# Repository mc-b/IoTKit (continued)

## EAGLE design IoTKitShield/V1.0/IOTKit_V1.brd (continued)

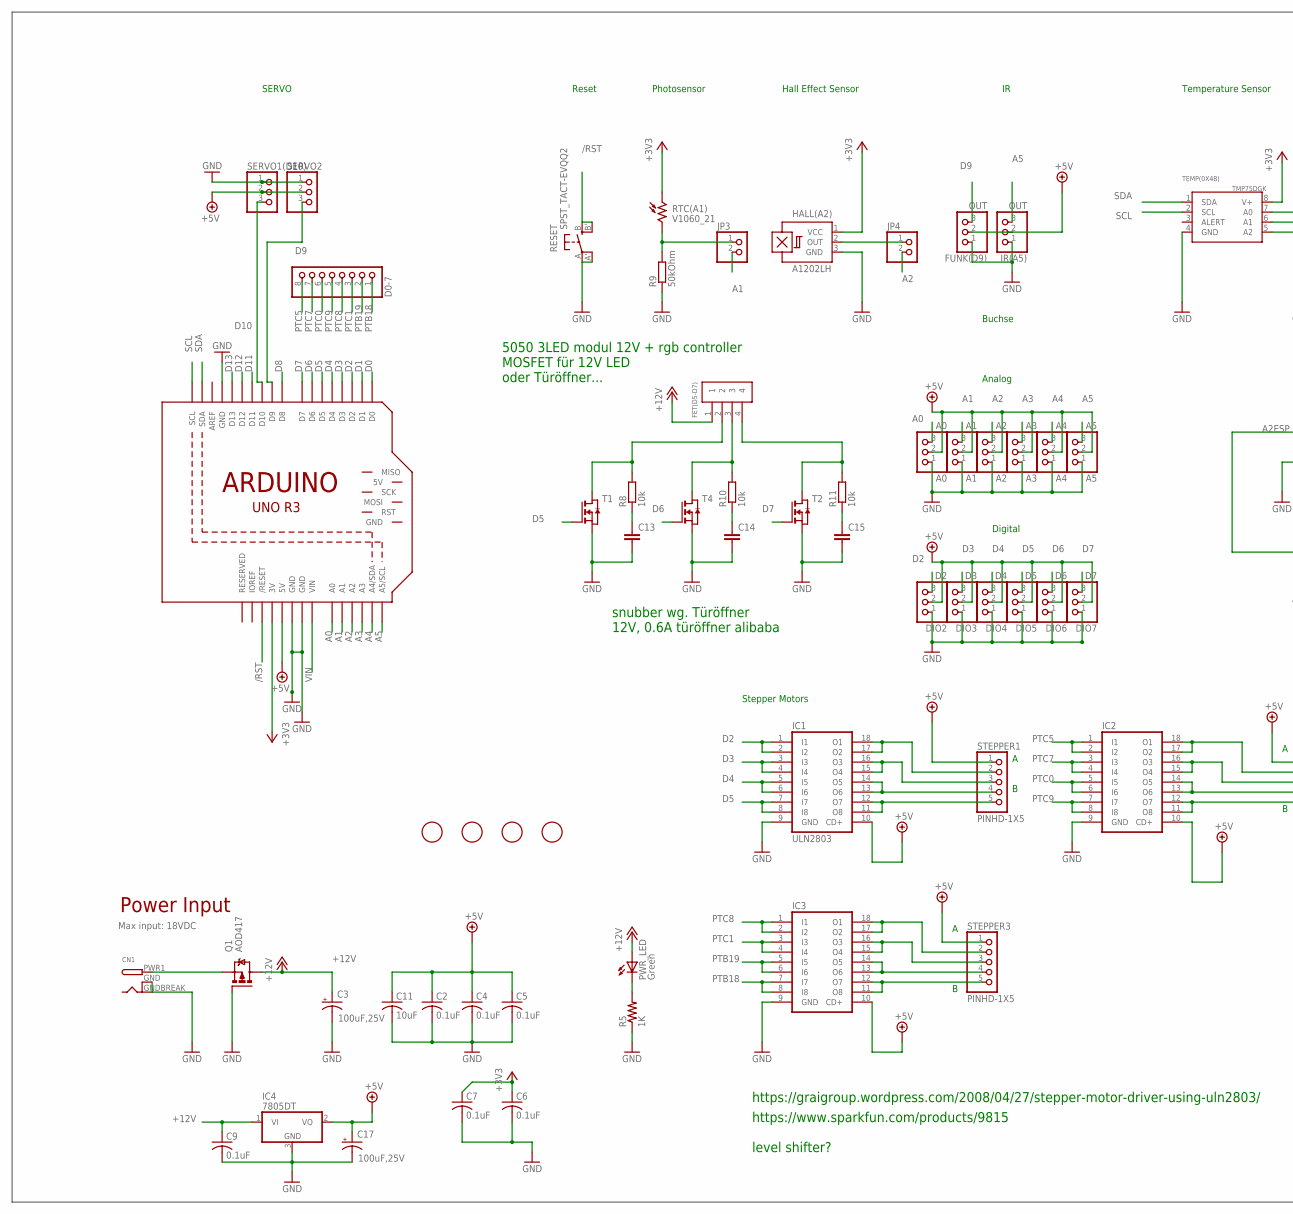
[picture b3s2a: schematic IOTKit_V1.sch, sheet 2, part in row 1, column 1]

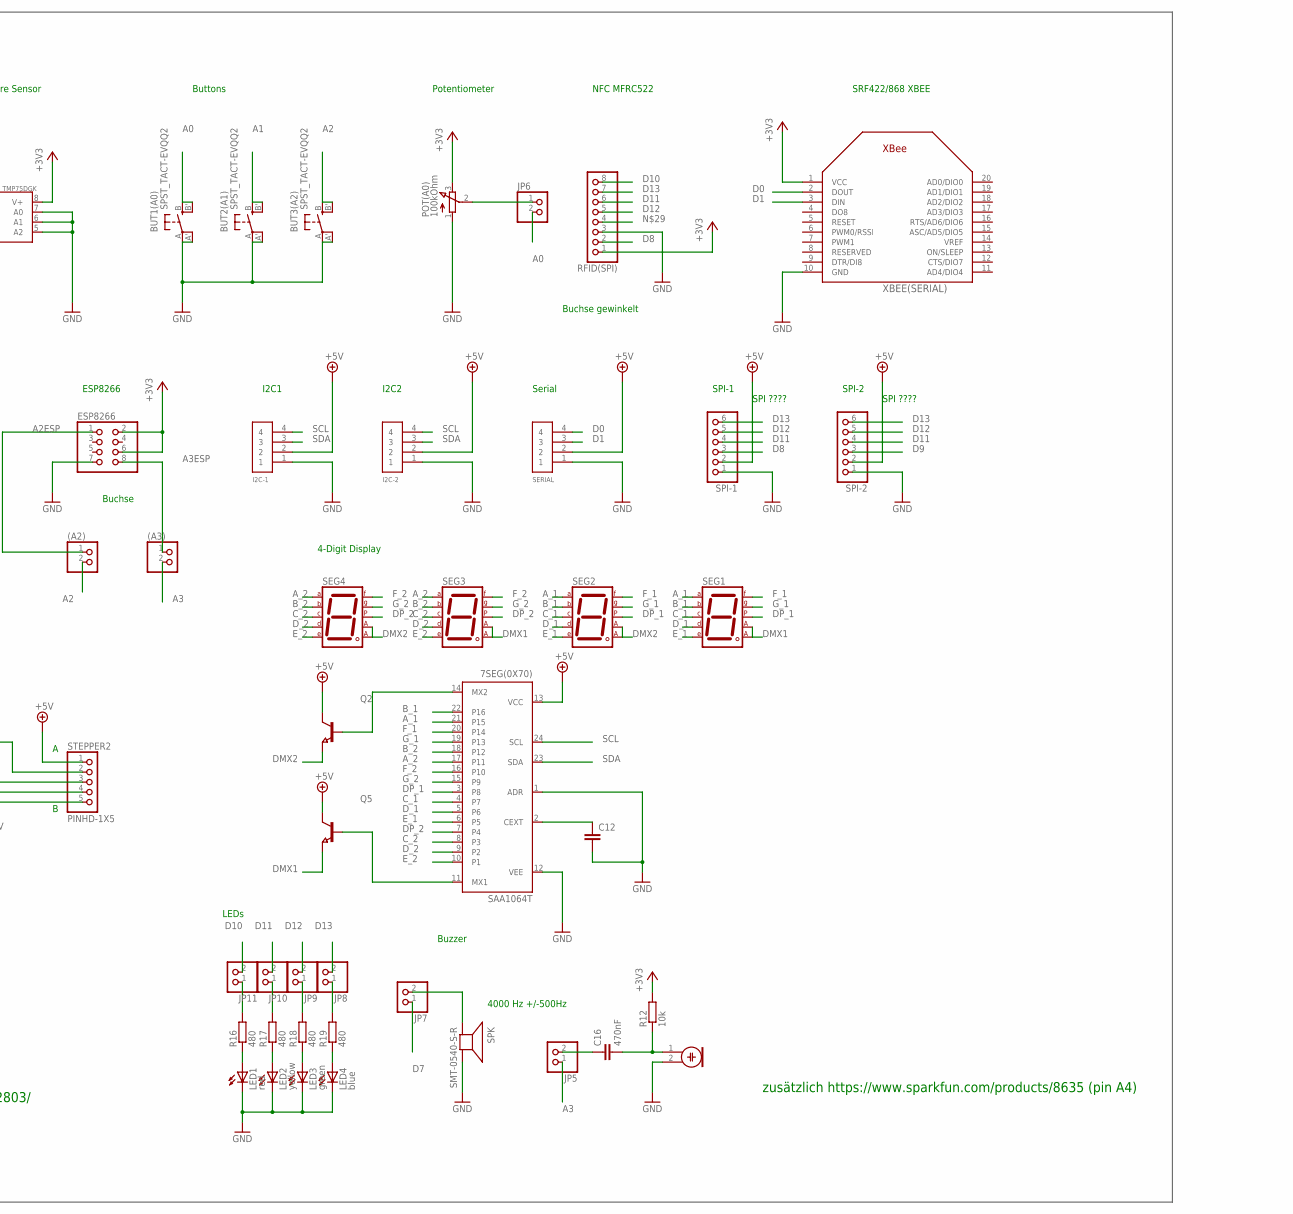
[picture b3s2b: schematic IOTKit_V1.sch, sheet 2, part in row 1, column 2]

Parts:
7SEG(0X70): SAA1064T; SO24
(A2), (A3): PINHD-1X2; 1X02_LINE
A0: A0; 1X03_LINE
A1: A1; 1X03_LINE
A2: A2; 1X03_LINE
A3: A3; 1X03_LINE
A4: A4; 1X03_LINE
A5: A5; 1X03_LINE
BUT1(A0), BUT2(A1), BUT3(A2): SPST_TACT-EVQQ2; EVQ-Q2
C2, C4, C5, C6, C7: 0.1uF; C0603K
C3, C17: 100uF,25V; NIPPON_F80
C9: 0.1uF; C0805K
C11: 10uF; C0805K
C12, C13, C14, C15: C-EUC0603; C0603
C16: 470nF; C0603
CN1: DCBARRELSMT; DCJACK_2MM_SMT
D0-7: PINHD-1X8CLEANBIG; 1X08-CLEANBIG
DIO2: D2; 1X03_LINE
DIO3: D3; 1X03_LINE
DIO4: D4; 1X03_LINE
DIO5: D5; 1X03_LINE
DIO6: D6; 1X03_LINE
DIO7: D7; 1X03_LINE
ESP8266: PINHD-2X4; 2X04
FET(D5-D7): 1X4; 1X04_LINE
FUNK(D9): OUT; 1X03_LINE
HALL(A2): A1202LH; SOT23-W
I2C-1, I2C-2: 1X4; 1X04_LINE
IC1: ULN2803; SO18W
IC2, IC3: ULN2803ASO18W; SO18W
IC4: 7805DT; TO252
IR(A5): OUT; 1X03_LINE
JP3, JP4, JP5, JP6, JP7, JP8, JP9, JP10, JP11: PINHD-1X2; 1X02_LINE
LED1: red; CHIP-LED0603
LED2: yellow; CHIP-LED0603
LED3: green; CHIP-LED0603
LED4: blue; CHIP-LED0603
MIC(A3): ELECTRET_MICROPHON-WM-62PC/62PK; WM-62PC/62PK
POT(A0): 100kOhm; EVUF
PWR_LED: Green; CHIP-LED0805
Q1: AOD417; D-PAK_TO252AA
Q2, Q5: NPN-TRANSISTOR_SOT23; SOT23
R5: 1K; R0805
R8, R10, R11: 10k; R0805
R9: 50kOhm; R0603
R12: 10k; R0603
R16, R17, R18, R19: 480; R0603
RESET: SPST_TACT-EVQQ2; EVQ-Q2
RFID(SPI): PINHD-1X8BIG; 1X08-BIG
RTC(A1): V1060_21; TO-5_V10
SEG1, SEG2, SEG3, SEG4: 7SEG-MCK; 7SEG-7
SERIAL: 1X4; 1X04_LINE
SERVO1(D10), SERVO2: PINHD-1X3; 1X03
SPI-1, SPI-2: PINHD-1X6B; 1X06-BIG
SPK: SMT-0540-S-R
STEPPER1, STEPPER2, STEPPER3: PINHD-1X5; 1X05
T1, T2, T4: NMOSSOT223; SOT223
TEMP(0X48): TMP75DGK; MSOP8
U$1, U$2, U$3, U$6: FIDUCIAL; FIDUCIAL_1MM
U$5: ARDUINO_R3_ICSP_NODIM; ARDUINOR3_ICSP_NODIM
XBEE(SERIAL): XBEE

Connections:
+3V3: C6.1, C7.1, ESP8266.2, ESP8266.6, HALL(A2).1 (VCC), POT(A0).3 (E), R12.2, RFID(SPI).1, RTC(A1).1, TEMP(0X48).8 (V+), U$5.3V, XBEE(SERIAL).1 (VCC)
+5V: 7SEG(0X70).13 (VCC), A0.2, A1.2, A2.2, A3.2, A4.2, A5.2, C2.1, C4.1, C5.1, C11.1, C17.+, DIO2.2, DIO3.2, DIO4.2, DIO5.2, DIO6.2, DIO7.2, FUNK(D9).2, I2C-1.2, I2C-2.2, IC1.10 (CD+), IC2.10 (CD+), IC3.10 (CD+), IC4.2 (VO), IR(A5).2, Q2.3 (C), Q5.3 (C), SERIAL.2, SERVO1(D10).2, SERVO2.2, SPI-1.2, SPI-2.2, STEPPER1.1, STEPPER2.1, STEPPER3.1, U$5.5V; also elsewhere on the board
+12V: C3.+, C9.1, FET(D5-D7).1, IC4.1 (VI), PWR_LED.A, Q1.4 (D); also elsewhere on the board
/RST: RESET.B (S), RESET.B' (S1), U$5.RESET (/RESET)
A0: A0.3, BUT1(A0).B (S), BUT1(A0).B' (S1), JP6.2, U$5.A0
A1: A1.3, BUT2(A1).B (S), BUT2(A1).B' (S1), JP3.2, U$5.A1
A2: (A2).2, A2.3, BUT3(A2).B (S), BUT3(A2).B' (S1), JP4.2, U$5.A2
A2ESP: (A2).1, ESP8266.1
A3: (A3).2, A3.3, JP5.1, U$5.A3
A3ESP: (A3).1, ESP8266.8
A4: A4.3, U$5.A4 (A4/SDA)
A5: A5.3, IR(A5).3, U$5.A5 (A5/SCL)
A_1: 7SEG(0X70).21 (P15), SEG1.7 (A), SEG2.7 (A)
A_2: 7SEG(0X70).17 (P11), SEG3.7 (A), SEG4.7 (A)
B_1: 7SEG(0X70).22 (P16), SEG1.6 (B), SEG2.6 (B)
B_2: 7SEG(0X70).18 (P12), SEG3.6 (B), SEG4.6 (B)
C_1: 7SEG(0X70).4 (P7), SEG1.4 (C), SEG2.4 (C)
C_2: 7SEG(0X70).8 (P3), SEG3.4 (C), SEG4.4 (C)
D0: SERIAL.4, U$5.D0, XBEE(SERIAL).2 (DOUT)
D1: SERIAL.3, U$5.D1, XBEE(SERIAL).3 (DIN)
D2: DIO2.3, IC1.1 (I1), IC1.2 (I2), U$5.D2; also elsewhere on the board
D3: DIO3.3, IC1.3 (I3), IC1.4 (I4), U$5.D3; also elsewhere on the board
D4: DIO4.3, IC1.5 (I5), IC1.6 (I6), U$5.D4; also elsewhere on the board
D5: DIO5.3, IC1.7 (I7), IC1.8 (I8), T1.1 (G), U$5.D5; also elsewhere on the board
D6: DIO6.3, T4.1 (G), U$5.D6; also elsewhere on the board
D7: DIO7.3, JP7.1, T2.1 (G), U$5.D7; also elsewhere on the board
D8: RFID(SPI).2, SPI-1.3, U$5.D8
D9: FUNK(D9).3, SERVO2.3, SPI-2.3, U$5.D9
D10: JP11.2, RFID(SPI).8, SERVO1(D10).3, U$5.D10
D11: JP10.2, RFID(SPI).6, SPI-1.4, SPI-2.4, U$5.D11
D12: JP9.2, RFID(SPI).5, SPI-1.5, SPI-2.5, U$5.D12
D13: JP8.2, RFID(SPI).7, SPI-1.6, SPI-2.6, U$5.D13
DMX1: Q5.2 (E), SEG1.3 (CA1), SEG1.8 (CA2), SEG3.3 (CA1), SEG3.8 (CA2)
DMX2: Q2.2 (E), SEG2.3 (CA1), SEG2.8 (CA2), SEG4.3 (CA1), SEG4.8 (CA2)
DP_1: 7SEG(0X70).3 (P8), SEG1.5 (DP), SEG2.5 (DP)
DP_2: 7SEG(0X70).7 (P4), SEG3.5 (DP), SEG4.5 (DP)
D_1: 7SEG(0X70).5 (P6), SEG1.2 (D), SEG2.2 (D)
D_2: 7SEG(0X70).9 (P2), SEG3.2 (D), SEG4.2 (D)
E_1: 7SEG(0X70).6 (P5), SEG1.1 (E), SEG2.1 (E)
E_2: 7SEG(0X70).10 (P1), SEG3.1 (E), SEG4.1 (E)
F_1: 7SEG(0X70).20 (P14), SEG1.9 (F), SEG2.9 (F)
F_2: 7SEG(0X70).16 (P10), SEG3.9 (F), SEG4.9 (F)
GND: 7SEG(0X70).1 (ADR), 7SEG(0X70).12 (VEE), A0.1, A1.1, A2.1, A3.1, A4.1, A5.1, BUT1(A0).A, BUT1(A0).A' (P1), BUT2(A1).A, BUT2(A1).A' (P1), BUT3(A2).A, BUT3(A2).A' (P1), C2.2, C3.-, C4.2, C5.2, C6.2, C7.2, C9.2, C11.2, C12.2, C13.2, C14.2, C15.2, C17.-, CN1.GND (GNDBREAK), CN1.GNDBREAK (GND), DIO2.1, DIO3.1, DIO4.1, DIO5.1, DIO6.1, DIO7.1, ESP8266.7, FUNK(D9).1, HALL(A2).3 (GND), I2C-1.1, I2C-2.1, IC1.9 (GND), IC2.9 (GND), IC3.9 (GND), IC4.3 (GND), IR(A5).1, LED1.C, LED2.C, LED3.C, LED4.C, MIC(A3).2, POT(A0).1 (A), Q1.1 (G), R5.1, R9.1, RESET.A, RESET.A' (P1), RFID(SPI).3, SERIAL.1, SERVO1(D10).1, SERVO2.1, SPI-1.1, SPI-2.1, SPK.+ (-), T1.3 (S), T2.3 (S), T4.3 (S), TEMP(0X48).4 (GND), TEMP(0X48).5 (A2), TEMP(0X48).6 (A1), TEMP(0X48).7 (A0), U$5.GND, U$5.GND@1 (GND), U$5.GND@3 (GND), XBEE(SERIAL).10 (GND); also elsewhere on the board
G_1: 7SEG(0X70).19 (P13), SEG1.10 (G), SEG2.10 (G)
G_2: 7SEG(0X70).15 (P9), SEG3.10 (G), SEG4.10 (G)
unnamed: CN1.PWR1 (PWR), Q1.3 (S)
unnamed: JP3.1, R9.2, RTC(A1).2
unnamed: HALL(A2).2 (OUT), JP4.1
unnamed: C16.1, JP5.2
unnamed: JP6.1, POT(A0).2 (S)
unnamed: JP7.2, SPK.- (+)
unnamed: JP11.1, R16.2
unnamed: JP10.1, R17.2
unnamed: JP9.1, R18.2
unnamed: JP8.1, R19.2
unnamed: LED1.A, R16.1
unnamed: LED2.A, R17.1
unnamed: LED3.A, R18.1
unnamed: LED4.A, R19.1
unnamed: IC2.11 (O8), IC2.12 (O7), STEPPER2.5
unnamed: IC2.13 (O6), IC2.14 (O5), STEPPER2.4
unnamed: IC2.15 (O4), IC2.16 (O3), STEPPER2.3
unnamed: IC2.17 (O2), IC2.18 (O1), STEPPER2.2
unnamed: 7SEG(0X70).14 (MX2), Q2.1 (B)
unnamed: 7SEG(0X70).11 (MX1), Q5.1 (B)
unnamed: 7SEG(0X70).2 (CEXT), C12.1
unnamed: C13.1, R8.1
unnamed: FET(D5-D7).2, R8.2, T1.2 (D), T1.4 (D)
unnamed: C14.1, R10.1
unnamed: FET(D5-D7).3, R10.2, T4.2 (D), T4.4 (D)
unnamed: C15.1, R11.1
unnamed: FET(D5-D7).4, R11.2, T2.2 (D), T2.4 (D)
unnamed: C16.2, MIC(A3).1, R12.1
unnamed: IC1.11 (O8), IC1.12 (O7), STEPPER1.5
unnamed: IC1.13 (O6), IC1.14 (O5), STEPPER1.4
unnamed: IC1.15 (O4), IC1.16 (O3), STEPPER1.3
unnamed: IC1.17 (O2), IC1.18 (O1), STEPPER1.2
unnamed: IC3.11 (O8), IC3.12 (O7), STEPPER3.5
unnamed: IC3.13 (O6), IC3.14 (O5), STEPPER3.4
unnamed: IC3.15 (O4), IC3.16 (O3), STEPPER3.3
unnamed: IC3.17 (O2), IC3.18 (O1), STEPPER3.2
PTB18: D0-7.1, IC3.7 (I7), IC3.8 (I8)
PTB19: D0-7.2, IC3.5 (I5), IC3.6 (I6)
PTC0: D0-7.6, IC2.5 (I5), IC2.6 (I6)
PTC1: D0-7.3, IC3.3 (I3), IC3.4 (I4)
PTC5: D0-7.8, IC2.1 (I1), IC2.2 (I2)
PTC7: D0-7.7, IC2.3 (I3), IC2.4 (I4)
PTC8: D0-7.4, IC3.1 (I1), IC3.2 (I2)
PTC9: D0-7.5, IC2.7 (I7), IC2.8 (I8)
PWR_LED: PWR_LED.C, R5.2
SCL: 7SEG(0X70).24 (SCL), I2C-1.4, I2C-2.4, TEMP(0X48).2 (SCL), U$5.SCL
SDA: 7SEG(0X70).23 (SDA), I2C-1.3, I2C-2.3, TEMP(0X48).1 (SDA), U$5.SDA
VIN: U$5.VIN

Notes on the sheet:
ESP8266
Analog
Temperature Sensor
Buttons
Hall Effect Sensor
Reset
Photosensor
Potentiometer
I2C1
I2C2
Serial
SPI-1
SPI-2
SPI ????
Digital
4-Digit Display
Buzzer
4000 Hz +/-500Hz
LEDs
NFC MFRC522
SRF422/868 XBEE
https://www.sparkfun.com/products/9815
level shifter?
https://graigroup.wordpress.com/2008/04/27/stepper-motor-driver-using-uln2803/
MOSFET für 12V LED oder Türöffner...
5050 3LED modul 12V + rgb controller
snubber wg. Türöffner 12V, 0.6A türöffner alibaba
zusätzlich https://www.sparkfun.com/products/8635 (pin A4)
Stepper Motors
Power Input
Max input: 18VDC
Buchse
Buchse gewinkelt
SERVO

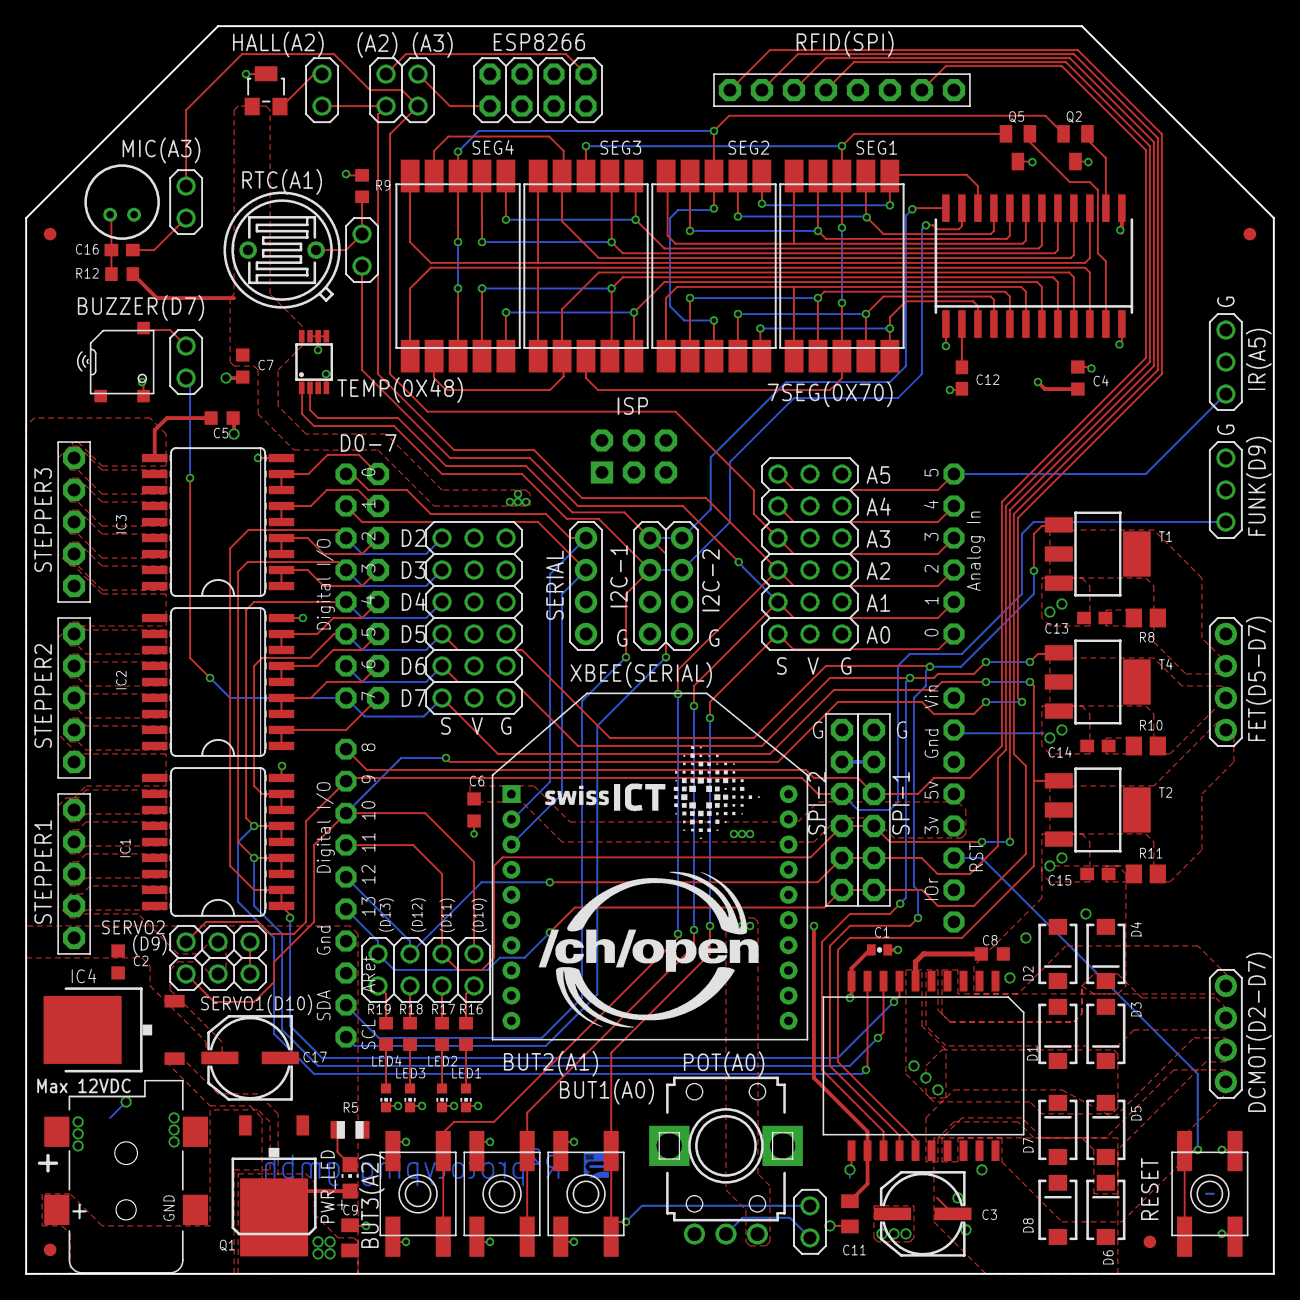
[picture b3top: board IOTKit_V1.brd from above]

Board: 2 copper layers, 99.1 x 99.1 mm, 113 parts (1 on the bottom side), 96 nets.

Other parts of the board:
U$4: R2_2MM

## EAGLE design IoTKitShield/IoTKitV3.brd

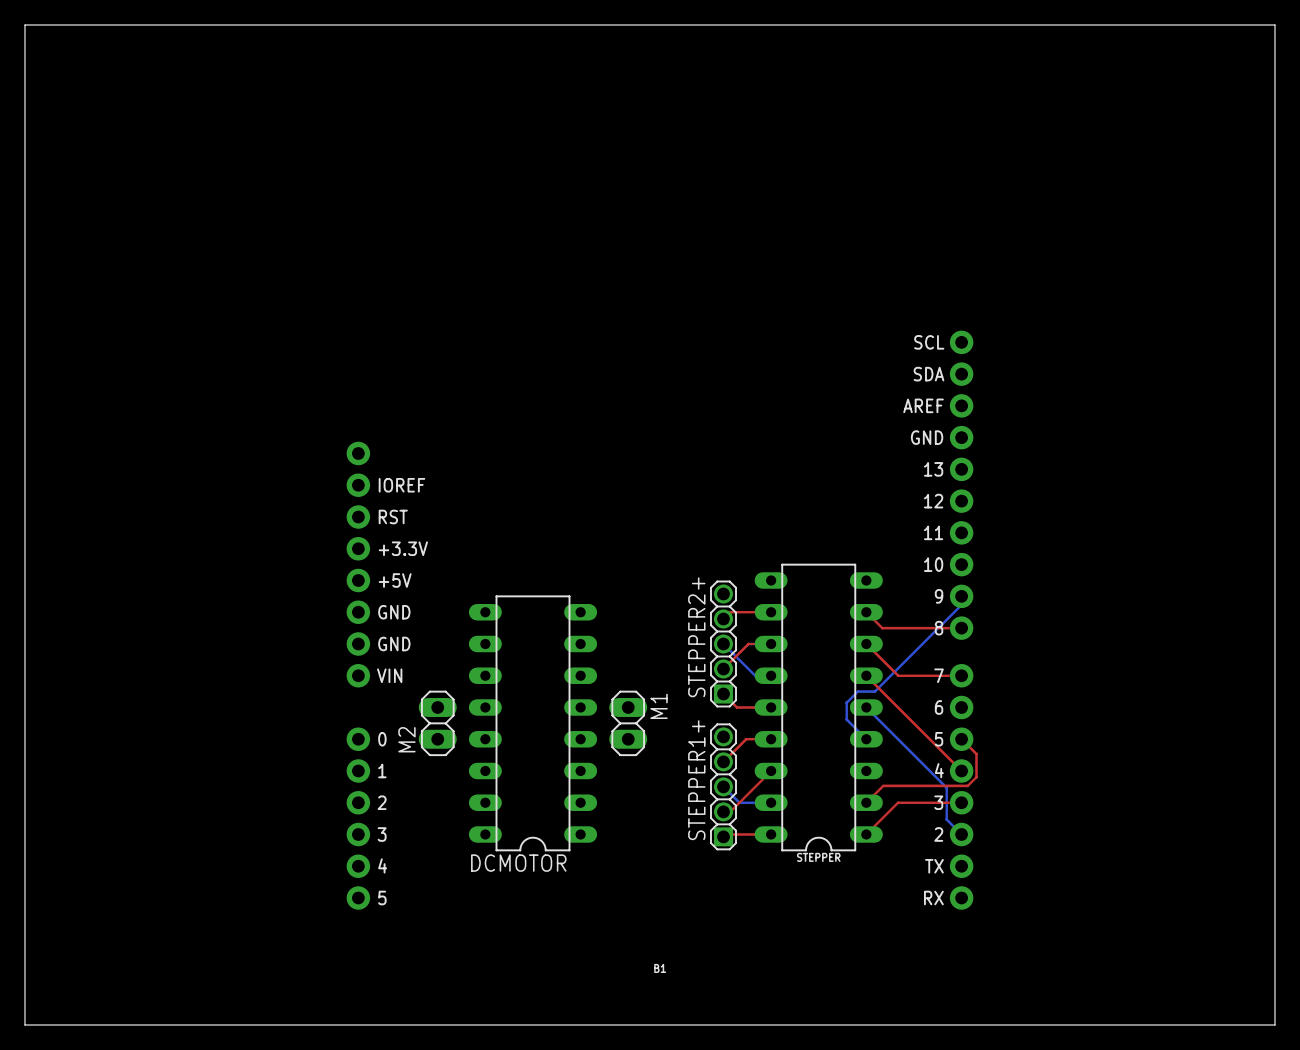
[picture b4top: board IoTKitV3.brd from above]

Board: 2 copper layers, 100.0 x 80.0 mm, 7 parts (0 on the bottom side), 22 nets.

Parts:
B1: ARDUINO_UNO_R3_SHIELDBASIC; UNO_R3_SHIELD
DCMOTOR: L293D; DIL16
M1, M2: 1X02
STEPPER: DIL18
STEPPER1+, STEPPER2+: 1_05X2MM

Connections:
+5V: B1.5V, DCMOTOR.8, DCMOTOR.16, STEPPER.10, STEPPER1+.5, STEPPER2+.5
D2: B1.D2, DCMOTOR.2, STEPPER.5
D3: B1.D3, DCMOTOR.1, STEPPER.1
D4: B1.D4, DCMOTOR.7, STEPPER.6
D5: B1.D5, DCMOTOR.9, STEPPER.2
D6: B1.D6, DCMOTOR.10, STEPPER.3
D7: B1.D7, DCMOTOR.15, STEPPER.7
D8: B1.D8, STEPPER.8
D9: B1.D9, STEPPER.4
GND: B1.GND@0, B1.GND@1, B1.GND@2, DCMOTOR.4, DCMOTOR.5, DCMOTOR.12, DCMOTOR.13, STEPPER.9
unnamed: STEPPER.18, STEPPER1+.1
unnamed: STEPPER.17, STEPPER1+.2
unnamed: STEPPER.16, STEPPER1+.3
unnamed: STEPPER.15, STEPPER1+.4
unnamed: STEPPER.14, STEPPER2+.1
unnamed: STEPPER.13, STEPPER2+.2
unnamed: STEPPER.12, STEPPER2+.3
unnamed: STEPPER.11, STEPPER2+.4
unnamed: DCMOTOR.3, M1.2
unnamed: DCMOTOR.6, M1.1
unnamed: DCMOTOR.14, M2.1
unnamed: DCMOTOR.11, M2.2

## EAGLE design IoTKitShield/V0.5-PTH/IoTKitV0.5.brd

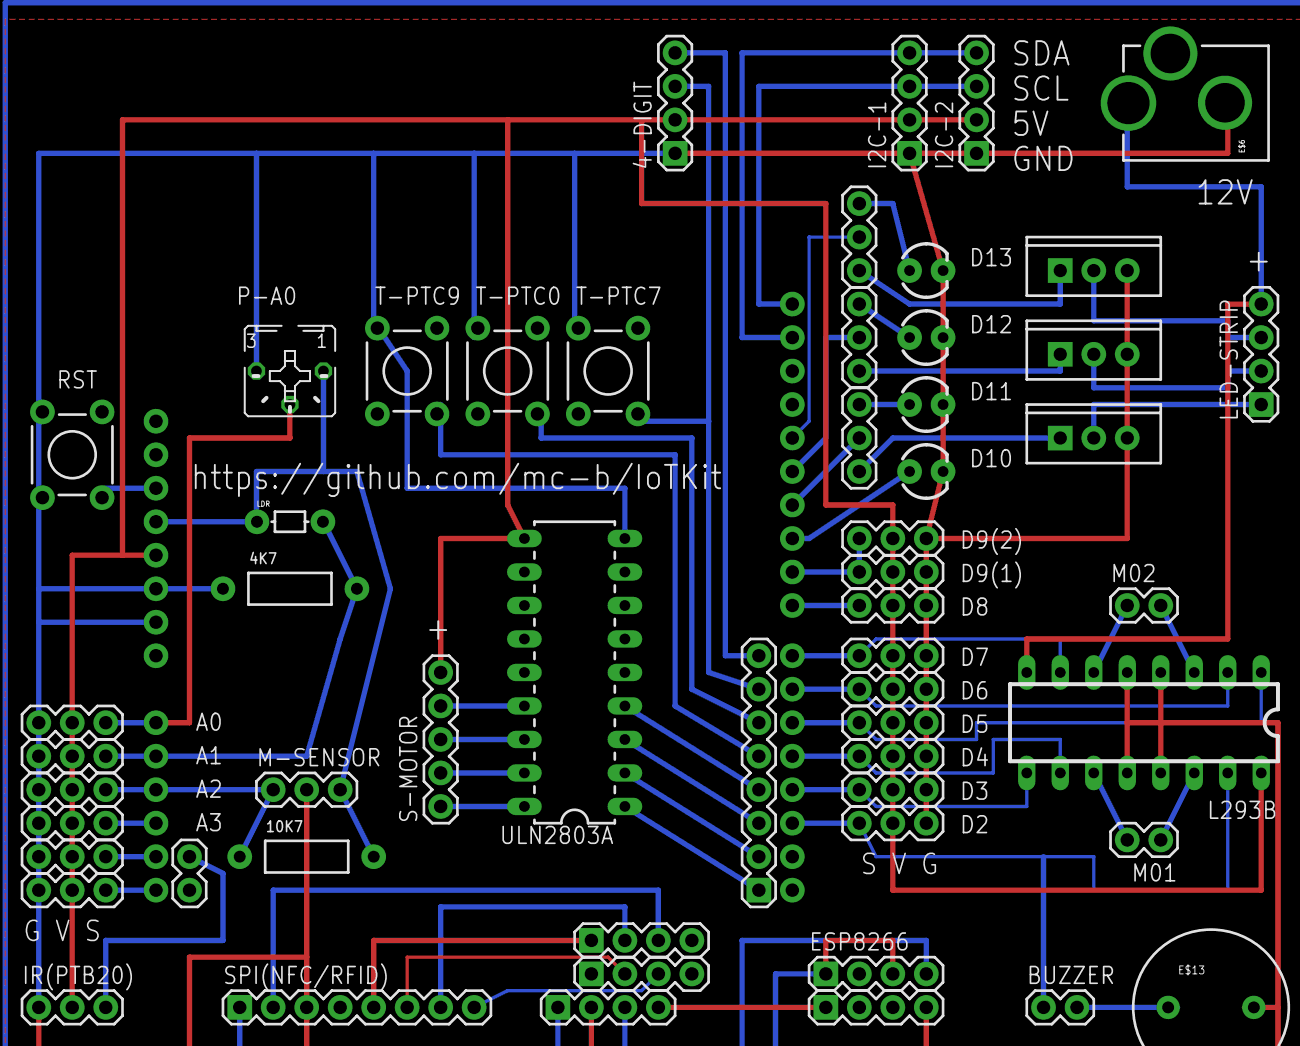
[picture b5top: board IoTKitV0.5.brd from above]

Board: 2 copper layers, 56 parts (0 on the bottom side), 56 nets.

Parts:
4-DIGIT: 1X04
4K7, 10K7: AXIAL-0.4
A0, A1, A2, A3, A4, A5: 1X03
BUZZER: 1X02
D2, D3, D4, D5, D6, D7, D8, D9(1), D9(2): 1X03
D10, D11, D12, D13: LED3MM
E$1: UNO_R3_SHIELD_NOLABELS
E$2, E$3, E$4: TO220-IGO
E$5: 1X08
E$6: POWER_JACK_PTH_LOCK
E$7, E$9, E$15: 1X03
E$8: 1X02
E$10, E$11, E$12, E$14: 1X04
E$13: BUZZER-12MM
ESP8266: 1X04
I2C-1, I2C-2: 1X04
IR(PTB20): 1X03
L293B: DIL16
LDR: AXIAL-5MM
LED-STRIP: 1X04
M01, M02: 1X02
M-SENSOR: 1X03
P-A0: B25P
RST: TACTILE-PTH
S-MOTOR: 1X05
SPI(NFC/RFID): 1X08
T-PTC0, T-PTC7, T-PTC9: TACTILE-PTH
ULN2803A: DIL18

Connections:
3V3: 10K7.P$2, E$1.3.3V, M-SENSOR.3, P-A0.A
5V: 4-DIGIT.2, A0.2, A1.2, A2.2, A3.2, A4.2, A5.2, D2.2, D3.2, D4.2, D5.2, D6.2, D7.2, D8.2, D9(1).2, D9(2).2, E$1.5V, I2C-1.2, I2C-2.2, IR(PTB20).2, L293B.16, S-MOTOR.5, ULN2803A.10
GND: 4-DIGIT.1, 4K7.P$1, A0.3, A1.3, A2.3, A3.3, A4.3, A5.3, D2.3, D3.3, D4.3, D5.3, D6.3, D7.3, D8.3, D9(1).3, D9(2).3, D10.K, D11.K, D12.K, D13.K, E$1.GND@0, E$1.GND@1, E$2.OUT, E$3.OUT, E$4.OUT, E$12.2, E$14.4, I2C-1.1, I2C-2.1, IR(PTB20).1, L293B.4, L293B.5, L293B.12, L293B.13, M-SENSOR.2, P-A0.E, SPI(NFC/RFID).3, ULN2803A.9
S$1: E$12.1, ESP8266.1, ESP8266.3, SPI(NFC/RFID).1
S$2: E$4.GND, LED-STRIP.1
S$3: E$2.GND, LED-STRIP.2
S$4: E$3.GND, LED-STRIP.3
S$5: E$12.3, ESP8266.4
S$6: E$12.4, E$14.1
S$7: D9(1).1, D9(2).1, E$1.D9
S$8: 4-DIGIT.4, E$5.8
S$9: E$1.D11, E$15.2
S$10: E$1.D12, E$9.2
S$11: D8.1, E$1.D8
S$12: E$1.D13, E$7.2
S$14: D11.A, E$15.3
S$15: D12.A, E$9.3
S$16: D13.A, E$7.3
S$17: E$3.IN, E$7.1
S$19: E$5.1, ULN2803A.1
S$20: E$5.2, ULN2803A.2
S$21: E$5.3, ULN2803A.3
S$22: E$5.4, ULN2803A.4
S$23: S-MOTOR.1, ULN2803A.18
S$24: S-MOTOR.2, ULN2803A.17
S$25: S-MOTOR.3, ULN2803A.16
S$26: S-MOTOR.4, ULN2803A.15
S$27: L293B.6, M02.1
S$28: L293B.3, M02.2
S$29: L293B.14, M01.1
S$30: L293B.11, M01.2
S$31: E$2.IN, E$9.1
S$32: A3.1, E$1.A3
S$33: A4.1, E$1.A4
S$34: E$4.IN, E$15.1
S$35: A5.1, E$1.A5
S$36: 10K7.P$1, A2.1, E$1.A2, M-SENSOR.1
S$37: A0.1, E$1.A0, P-A0.S
S$38: E$10.3, SPI(NFC/RFID).2
S$39: E$11.3, SPI(NFC/RFID).8
S$40: E$10.2, SPI(NFC/RFID).7
S$41: E$10.1, SPI(NFC/RFID).5
S$42: E$11.2, SPI(NFC/RFID).6
S$50: 4K7.P$2, A1.1, E$1.A1
V12: L293B.8, LED-STRIP.4
W2: BUZZER.1, D2.1, E$1.D2, L293B.15
W3: D3.1, E$1.D3, L293B.9
W4: D4.1, E$1.D4, L293B.10
W5: D5.1, E$1.D5, L293B.1
W6: D6.1, E$1.D6, L293B.2
W7: D7.1, E$1.D7, L293B.7
W10: D10.A, E$1.D10
WB20: E$8.2, IR(PTB20).3
WC9: 4-DIGIT.3, E$5.7
WSCL: E$1.SDA, I2C-1.4, I2C-2.4
WSDA: E$1.SCL, I2C-1.3, I2C-2.3

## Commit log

2015-03-13 Einfache Web-App
2015-03-13 Falscher Dateiname
2015-08-05 Beispiele fuer lokale Compilation
2015-08-05 Beispiel fuer lokale Compilation (nur Beispiel Makefile)
2015-08-15 Ausgesuchte Testprogramme adaptiert auf Eclipse und gcc4mbed
2015-08-28 Eclipse SmartHome Binding fuer IoTKit SMD Shield
2015-08-28 Temp (I2C) und RGB LED Strip impl.
2015-09-07 Copyright bereinigt
2015-09-14 Im Original auf mbed.org geaendert
2015-09-14 Steuert jetzt auf cygwin zu
2015-11-05 Dockerfile fuer leshan
2015-11-05 Beschreibung
2015-11-05 Test und Infrastruktur ergaenzt
2015-11-05 Apache REST Docker Image
2015-11-05 Integration MySQL
2015-11-05 Formatierung
2015-11-05 Format
2015-11-13 Feintuning
2015-11-13 IoTKit Shield Version 0.5 und V1.0
2015-11-13 IoTKit Version V2.0
2015-11-13 Modem Korrekturen
2015-11-13 Detailkorrekturen
2015-11-13 Beschreibungen
2015-11-13 CAD Teile zum IoTKit
2015-11-13 CAD Teile
2015-11-13 Makefile um Docker zu vereinfachen
2015-11-13 Makefile
2015-11-13 mosquitto Docker image fuer IoTKit
2015-11-13 openhab2 Docker
2015-11-13 Jenkins Docker Image
2015-11-13 Platzhalter weitere Images
2015-11-13 FROM Versionen abgestimmt
2015-11-14 Wetty (Web + tty) Image
2015-11-14 Ergaenzt
2015-11-14 Globaler Makefile
2015-11-14 clean
2015-11-14 Hostname setzen
2015-11-14 Apache Reverse Proxy und Ports abgestimmt
2015-11-14 Grundkonfiguration
2015-11-14 Bereinigt
2015-11-14 Feintuning - Zugriff auf MySQL Server
2015-11-14 FHEM Image
2015-11-15 Test Proxy Einstellungen
2015-11-15 Relative statt fixe URL's
2015-11-15 Kura Grundimage
2015-11-15 Fehler apt-get update erledigt
2015-11-16 Repository wetty autom. holen beim builden
2015-11-16 init.d Initscript um alle Docker Container zu starten
2015-11-16 stop verschnellert
2015-11-16 Explizites Stoppen bei make run
2015-11-16 alten Container bei run verwerfen
2015-11-16 Startup fuer Docker Images
2015-11-17 Zip HACK eleminiert
2015-11-17 Mosquitto Server
2015-11-17 Ergaenzt um CoAP
2015-11-17 Optimiert
2015-11-17 Logs eingefuegt
2015-11-17 Usage eingefuert
2015-11-17 Kommentar verbessert
2015-11-17 Ergaenzt um LWM2M Client
2015-11-18 Ausgabe Pub Message auf stdout
2015-11-18 cgi-bin Script um Docker Logs im Browser auszugeben
2015-11-19 IotKit Beispiele ergaenzt
2015-11-22 ThingSpeak Image
2015-11-22 thingSpeak nachgetragen
2015-11-22 Netzwerk uebersicht
2015-11-23 Zusteuerung neuste Doker Version
2015-11-23 Cordova Grundgeruest
2015-11-23 Abgestimmt mit Android SDK Version
2015-11-23 simpleAPP abgestimmt auf Apache Cordova
2015-11-23 Optimiert, Jenkins Jobs
2015-11-23 Umfangreicheres Beispiel
2015-11-23 IoTKit App Sample
2015-11-23 cd korrigiert
2015-11-23 Release entfernt gibt Probleme beim Installieren
2015-11-24 GCC4mbed und mbed V2 Job eingefuegt
2015-11-24 Volume um Container als Build Umgebung zu verwenden
2015-11-26 web-terminal als Alternative zu wetty
2015-11-26 Jenkins Jobs
2015-11-26 Script fuer Netzwerkuebersicht
2015-11-27 Eigene Jenkins Umgebung fuer Java Jobs erstellt.
2015-11-27 Anpassungen Raspberry Pi
2015-11-28 Proxy Material
2015-11-28 iot-stick Umgebung
2015-11-28 Installation Docker und Standard Umgebung - nicht getestet
2015-11-28 : fehlte
2015-11-28 Falsches Verzeichnis
2015-11-28 Start Docker bei Systemstart
2015-11-28 Push und Pull
2015-11-28 Fehlerkorrektur, Erweiterung pull Rasppberry Pi
2015-11-28 Ausfuehrbarbit gesetzt
2015-11-28 RPi Korrekturen
2015-11-29 Umgestellt auf restart=always
2015-11-29 Fehlender restart=always nachgetragen
2015-11-30 Web-App integriert und Anzeige SQL
2015-11-30 Titel
2015-11-30 Einleitung
2015-11-30 Copyright
2015-11-30 Vereinfacht
2015-11-30 Weitere Beispiele
2015-11-30 Nur 1 Build Prozessor - mehr geben Probleme
2015-11-30 smd.iotkit2.ch
2015-11-30 smd.iotkit2.ch Beispiel
2015-11-30 Tooltips ergaenzt
2015-11-30 Reverse Proxy Einstellungen ueberarbeitet
2015-12-02 Reverse Proxy verbessert
2015-12-02 Obsolet
2015-12-02 Eigenes Verzeichnis
2015-12-02 Installation
2015-12-02 Name bereinigt
2015-12-02 Verzeichnis angepasst
2015-12-02 Echo korrigiert
2015-12-02 Logname statt User ID
2015-12-03 Korrekturen fuer Raspberry Pi
2015-12-03 clone wetty obsolet
2015-12-03 lokale git clone in Dockerfile verschoben
2015-12-03 show
2015-12-03 Swapfile
2015-12-04 Neues Verzeichnis
2015-12-04 Erstellt mit openhab2
    https://github.com/openhab/openhab2/blob/master/docs/sources/development/bindings.md
2015-12-04 Abgeloest durch smarthome/org.openhab.binding.iotkit
2015-12-04 IoTKit Binding Job
2015-12-04 Links zum IoTKit Bindings Plug-In angepasst
2015-12-05 sudo ohne Password
2015-12-06 Abgespeckt zu viele Schritte fuer Docker
2015-12-06 Jenkins um Web IDE ergaenzt
2015-12-06 Maven um IDE ergaenzt
2015-12-06 Rekursion entfernt
2015-12-06 Erweiterung Maven Image um IDE
2015-12-06 IDE integriert - run: jenkins, maven, cordova deaktiviert
2015-12-06 Zugriff auf Host workspace entfernt
2015-12-06 Test
2015-12-07 Codebox laeuft als jenkins User
2015-12-07 codebox as jenkins
2015-12-07 Cordova IDE hinter Proxy
2015-12-07 bash History Verbindung mosquitto, leshan, rest
2015-12-07 Falscher Titel
2015-12-07 maven-ide statt maven auf RPi
2015-12-10 Erweiterungen Raspberry Pi
2015-12-10 Korrekturen Raspberry Pi
2015-12-10 cgit Integration
2015-12-10 Verzeichnis
2015-12-31 IoTKit Server
2015-12-31 Vagrant Setup
2015-12-31 Yotta und GCC4ARM ergaenzt
2016-01-01 Port fuer Remote Desktop
2016-01-01 Modularisiert
2016-01-04 CFLF entfernt
2016-01-04 Sourcen und Container getrennt
2016-01-20 Packer: IoT Server Grundimages
2016-01-20 Image vom Internet holen
2016-01-20 Eigene Abhandlung VBox Guest Install
2016-01-21 Falscher Path fuer GCC4ARM
2016-01-29 Port 5683/udp oeffnen, apt-update wegen Fehler apache2 Install
2016-03-04 SwiSMA Vortrag vom 4.3.16
2016-03-05 Scratch, Gerbv und CAMotics neu installieren
2016-03-05 GCC 4 ARM Update
2016-03-05 SwiSMA Folien
2016-03-06 Weitere CAD/CNC Programme
2016-03-06 Raspberry Pi Installationsdateien - nicht gestestet
2016-03-06 Scratch
2016-03-07 pi statt raspberry
2016-03-07 NOOBS - nicht getestet
2016-03-07 Feinkorrekturen
2016-03-07 root FS falsch
2016-03-19 FIXME und TODO als Beispiel fuer jenkins angefuegt
2016-03-19 AdHoc = LAM Server
2016-03-19 Hostname, email (postfix), cppcheck
2016-03-19 Standardport http-alt statt 8000
2016-03-19 hostname iot-server, email (postfix), TZ, Keyboard
2016-03-19 Korrektur apt-get update
2016-03-19 Variable IP Adresse
2016-03-20 https statt http
2016-03-20 Jenkins Plug-Ins Taskscanner, CPPCheck
2016-03-20 Detailkorr
2016-03-20 CPP Check und TODO
2016-03-20 Problem mit gt
2016-03-21 User
2016-03-21 Alle Projekte
2016-03-21 Anweisungen
2016-03-21 Hinweis copy
2016-03-31 Vortrag anlaesslich Lernstick Community Treffen
2016-04-03 Help
2016-04-09 cgit raus
2016-04-15 restsql mit HTTP GET fuer showsql
2016-05-29 Robot Web App
2016-05-29 Einbindung IoTKit Robot APP
2016-05-29 Falscher Name
2016-07-16 Informatiktage Talks
2016-07-16 Update README.md
    new talks
2016-07-17 Ubuntu 14.04
2016-07-17 leshan Download links
2016-07-17 Arguments
2016-08-29 Talk Normen und Standards
2016-09-02 Update Workshops
2016-09-11 Einstellungen nginx als Alternative zu Apache2
2016-09-17 Vortraege Maker Faire Zuerich
2016-09-18 Kurse ergaenzt
2016-10-27 Umbau von yotta auf mbed-cli
2017-05-14 Formatierungsfehler
2017-05-14 Kurse
2017-08-09 Eclipse Projekt
2017-08-14 Bilder zu IoTKit
2017-08-14 Talks
2017-08-14 Talks und Links IoTKit V1 + V2
2017-08-14 Fehler
2017-08-25 Mini Maker Faire
2017-08-26 Links
2018-09-08 IoTKit V3
2018-09-08 Update Kurse
2018-09-08 Link
2018-09-12 Kurse updated
2018-10-21 IoTKit V3 th
2018-10-21 routed
2018-10-22 Version fuer Produktion
2018-10-26 Textkorrekturen
2018-10-27 Korrekturen NFC, Hallsensor, Servos
2019-03-03 In IoTKitV3_disco Repository
2021-08-10 EB raus
2025-04-24 backstage.io
